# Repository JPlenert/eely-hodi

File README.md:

# eely-HoDi

Home of the Eely Home Display (HoDi) (https://www.eely.eu).

HoDi is a 64x32 matrix LED display driven by a ESP32 that shows:

* the current time
* energy consumptions (with shelly sensors)
* energy productions (with shelly sensors)
* temperatures (with shelly sensors)
* energy prices (with tibber)

## How to build

* Clone repository with `--recursive` to clone the submodules
* Install esbuild with `npm install` in the web folder

* Build eely-hodi-web for release
* Build eely-hodi-esp

Uses ESP-IDF V5.3 for espressif ESP32.

## Remark

This a private hobbyist (aka maker) project that helps me to ['sharpen the saw'](https://blog.codinghorror.com/sharpening-the-saw/) as a Director of a Software innovation unit.
Since I'm more a "backend guy" (white characters on black screen), the frontend is a really "quick and DIRTY" implementation!

## License

eely-HoDi is distributed under the GPL v3 license:

    Copyright (C) 2022-2025 by Joerg Plenert

    This program is free software: you can redistribute it and/or modify
    it under the terms of the GNU General Public License as published by
    the Free Software Foundation, in version 3 of the License.

    This program is distributed in the hope that it will be useful,
    but WITHOUT ANY WARRANTY; without even the implied warranty of
    MERCHANTABILITY or FITNESS FOR A PARTICULAR PURPOSE.  See the
    GNU General Public License for more details.

    You should have received a copy of the GNU General Public License
    along with this program.  If not, see <https://www.gnu.org/licenses/>.

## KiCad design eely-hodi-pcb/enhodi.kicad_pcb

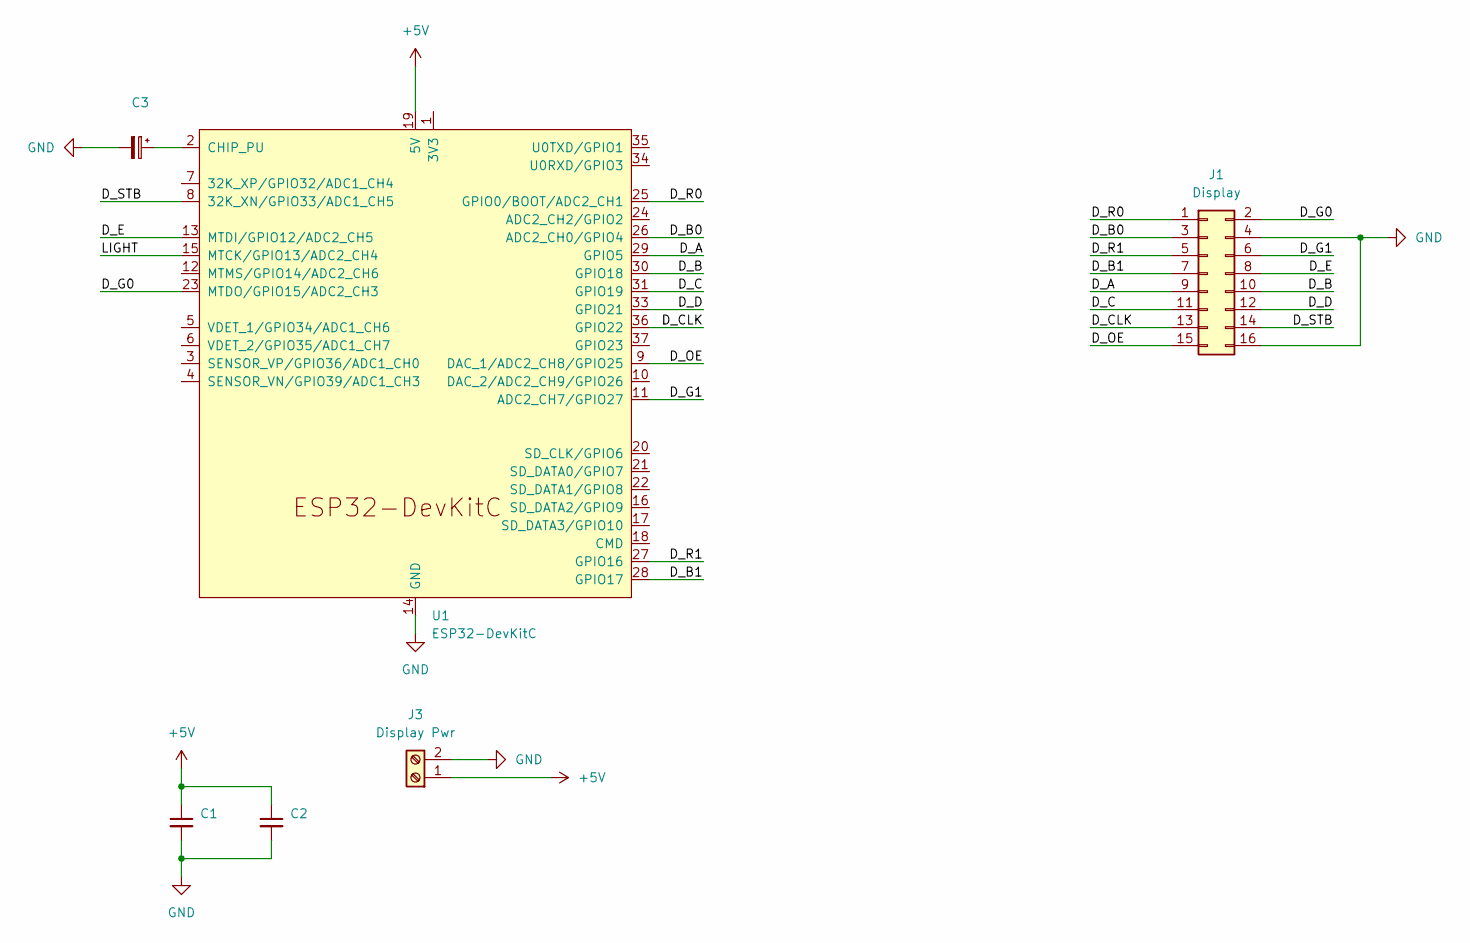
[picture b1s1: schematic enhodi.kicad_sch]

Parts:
C1, C2: C_Rect_L4.6mm_W3.0mm_P2.50mm_MKS02_FKP02
C3: CP_Radial_D5.0mm_P2.50mm
J1: Display; PinHeader_2x08_P2.54mm_Vertical
J3: Display Pwr; TerminalBlock_TE_282834-2_1x02_P2.54mm_Horizontal
U1: ESP32-DevKitC

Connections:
+5V: C1.1, C2.1, J3.1, U1.19 (5V)
/D_A: J1.9, U1.29 (GPIO5)
/D_B: J1.10, U1.30 (GPIO18)
/D_B0: J1.3, U1.26 (ADC2_CH0/GPIO4)
/D_B1: J1.7, U1.28 (GPIO17)
/D_C: J1.11, U1.31 (GPIO19)
/D_CLK: J1.13, U1.36 (GPIO22)
/D_D: J1.12, U1.33 (GPIO21)
/D_E: J1.8, U1.13 (MTDI/GPIO12/ADC2_CH5)
/D_G0: J1.2, U1.23 (MTDO/GPIO15/ADC2_CH3)
/D_G1: J1.6, U1.11 (ADC2_CH7/GPIO27)
/D_OE: J1.15, U1.9 (DAC_1/ADC2_CH8/GPIO25)
/D_R0: J1.1, U1.25 (GPIO0/BOOT/ADC2_CH1)
/D_R1: J1.5, U1.27 (GPIO16)
/D_STB: J1.14, U1.8 (32K_XN/GPIO33/ADC1_CH5)
/LIGHT: U1.15 (MTCK/GPIO13/ADC2_CH4)
GND: C1.2, C2.2, C3.2, J1.4, J1.16, J3.2, U1.14 (GND), U1.32 (GND), U1.38 (GND)
unnamed: C3.1, U1.2 (CHIP_PU)

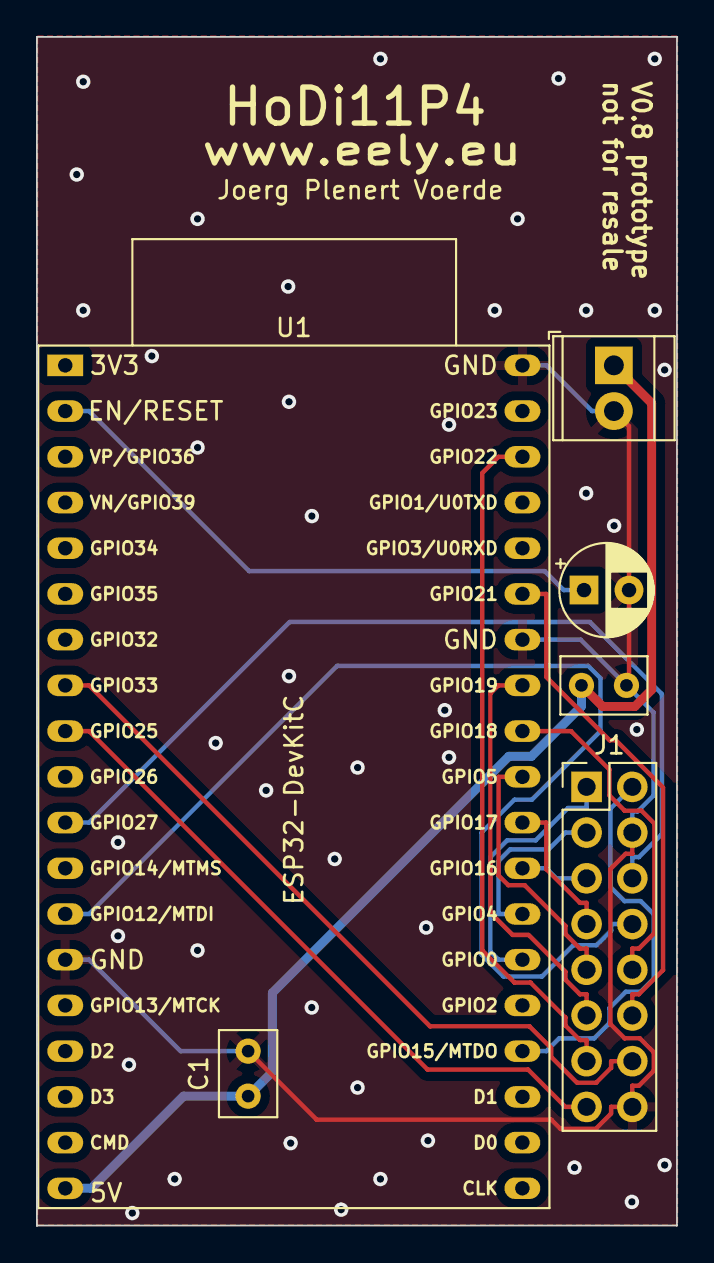
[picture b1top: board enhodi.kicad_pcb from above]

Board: 2 copper layers, 35.6 x 66.0 mm, 6 parts (0 on the bottom side), 17 nets.

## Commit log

2024-07-27 Inital release
2025-12-19 refactor: Moved to new web-base with preact feat: Added Shelly-EM and Shelly-Pro EM fix: Better error detection and messages on shelly connection fails
2025-12-19 fix: Added missing index.html
2025-12-19 doc: Additional information on how to build
2025-12-20 Added doc
2025-12-20 Added url switch for testing
2025-12-29 feat: Support for Shelly EM Gen1 and Gen3 devices fix: Energy display type with wrong inital value refactor: Enhanced internal handling for Shelly device generations
2025-12-29 fix: Invalid Shelly generation assignment
2026-01-04 feat: Updated to new eely-base-web doc: Updated Copyright
2026-01-04 doc: Updated Copyright
2026-01-04 Missing files
